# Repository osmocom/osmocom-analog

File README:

This software implements base station protocol of classic mobile phones. With
radio transmitter and receiver connected to one sound card and a headset
connected to another sound card, it is possible to make and receive calls to
and from mobile phone. With SDR (software defined radio) it can be use without
radio equipment connected to a sound card, and even multiple channels can be
generated simultaniously using SDR. Currently supported networks:

 * A-Netz
 * B-Netz (ATF-1)
 * C-Netz
 * NMT 450 / 900 (Nordic Mobile Telephone)
 * AMPS (Advanced Mobile Phone System)
 * TACS (Total Access Communication System)
 * JTACS (Japanese version of TACS)
 * Radiocom 2000 (French network)
 * IMTS / MTS ((Improved) Mobile Telephone Service)
 * MPT1327 (Trunked Radio) aka known as 'Buendelfunk'
 * Eurosignal (ERuRD paging service)
 * 5-Ton-Folge (ZVEI 5 tone paging code for pager and siren trigger)
 * JollyCom (Unofficial network, invented by the author)
 * C-Netz BSC (Connecting to a C-Netz Base Station)

Additionally the following communication services are implemented:

 * TV Transmitter with test Images
 * Radio transmitter / receiver
 * Analog Modem Emulation 'Datenklo' (AM7911)
 * German classic 'Zeitansage' (talking clock)
 * POCSAG transmitter / receiver
 * Golay/GSC transmitter / receiver
 * DCF77 time signal transmitter and receiver with weather info
 * C-Netz SIM emulator
 * C-Netz magnetic card emulator

USE AT YOUR OWN RISK!

Acknowledgements:

Carsten Wollesen for donating Telefunken 4015 B-Netz phone back in the 90's.

Klaus Adler for helping me to retrieve complete NMT specification and donating
a BSA44 (magnetic card C-Netz hackable phone) back in the 90's.

Andy Zauner for providing signaling specification of C-Netz back in the 90's.

Hans Wigger for providing valuable information about A-Netz and B-Netz and
helping me to get an A-Netz phone.

Stephan Hessberger for his work on oebl.de, that provides valuable information
about A-Netz, B-Netz, C-Netz, Eurosignal and much more.

Friedhelm Hillebrand for providing complete specification of the mobile phone
of C-Netz.

Mikko Ristila for providing newer NMT specs (with DMS/SMS specifications).

Dieter Spaar and Mark Atherton for providing AMPS information and recordings
to verify and debug AMPS support.
See http://www.idesignz.org/AMPS/AMPS_BS.html for first base station
implementation of AMPS.

Telecommunication Industry Association for providing TIA/EIA-533 documentation.
"Reproduced under written permission from Telecommunications Industry
Association."

Eric from Smart Card World and Karsten Niehusen from cardomatic.de for
providing memory cards to be programmed for older C-Netz phone.

Dieter Spaar providing TACS recordings to verify and debug TACS support.

Hans Wigger providing Radiocom 2000 recordings, to reverse-enigineer the
standard, which seems not to exist anymore...

Peter, Peter, Friedhelm and Stephan for providing documentation and hardware
for C-Netz Base Station and other C-Netz documents.

Carsten Wollesen for donating MPT1327 radios and programming tools.

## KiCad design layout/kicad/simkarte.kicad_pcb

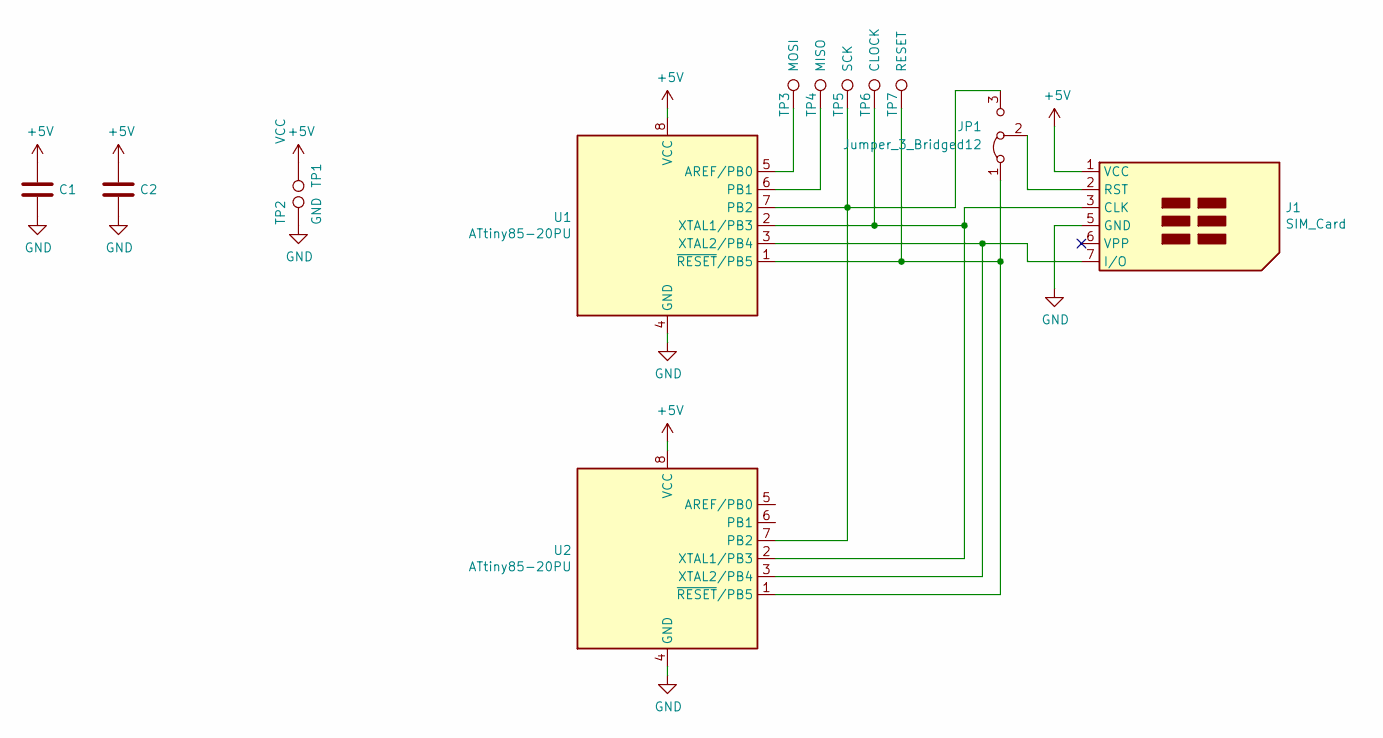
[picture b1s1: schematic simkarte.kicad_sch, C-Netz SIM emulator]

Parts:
C1, C2: C; C_0603_1608Metric
J1: SIM_Card; SIM-Pads
JP1: Jumper_3_Bridged12; SolderJumper-3_P1.3mm_Bridged12_RoundedPad1.0x1.5mm_NumberL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
TP1: VCC; tp_for_sim
TP2: GND; tp_for_sim
TP3: MOSI; tp_for_sim
TP4: MISO; tp_for_sim
TP5: SCK; tp_for_sim
TP6: CLOCK; tp_for_sim
TP7: RESET; tp_for_sim
U1: ATtiny85-20PU; SO-8_falschrum
U2: ATtiny85-20PU; DIP-8_W7.62mm_Socket

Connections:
+5V: C1.1, C2.1, J1.1 (VCC), TP1.1, U1.8 (VCC), U2.8 (VCC)
GND: C1.2, C2.2, J1.5 (GND), TP2.1, U1.4 (GND), U2.4 (GND)
unnamed: J1.2 (RST), JP1.2 (C)
unnamed: J1.3 (CLK), TP6.1, U1.2 (XTAL1/PB3), U2.2 (XTAL1/PB3)
unnamed: J1.7 (I/O), U1.3 (XTAL2/PB4), U2.3 (XTAL2/PB4)
unnamed: TP3.1, U1.5 (AREF/PB0)
unnamed: TP4.1, U1.6 (PB1)
unnamed: JP1.3 (B), TP5.1, U1.7 (PB2), U2.7 (PB2)
unnamed: JP1.1 (A), TP7.1, U1.1 (~RESET/PB5), U2.1 (~RESET/PB5)

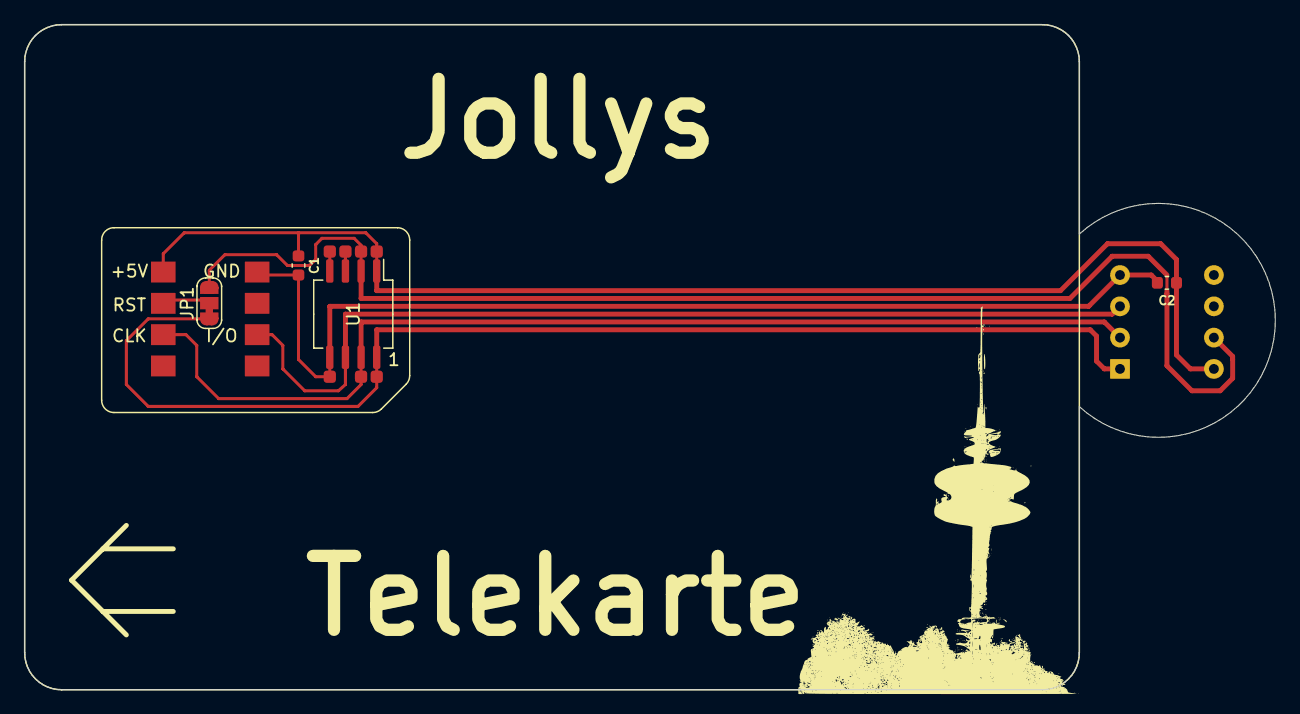
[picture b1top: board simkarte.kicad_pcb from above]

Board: 2 copper layers, 101.5 x 54.0 mm, 13 parts (1 on the bottom side), 9 nets.

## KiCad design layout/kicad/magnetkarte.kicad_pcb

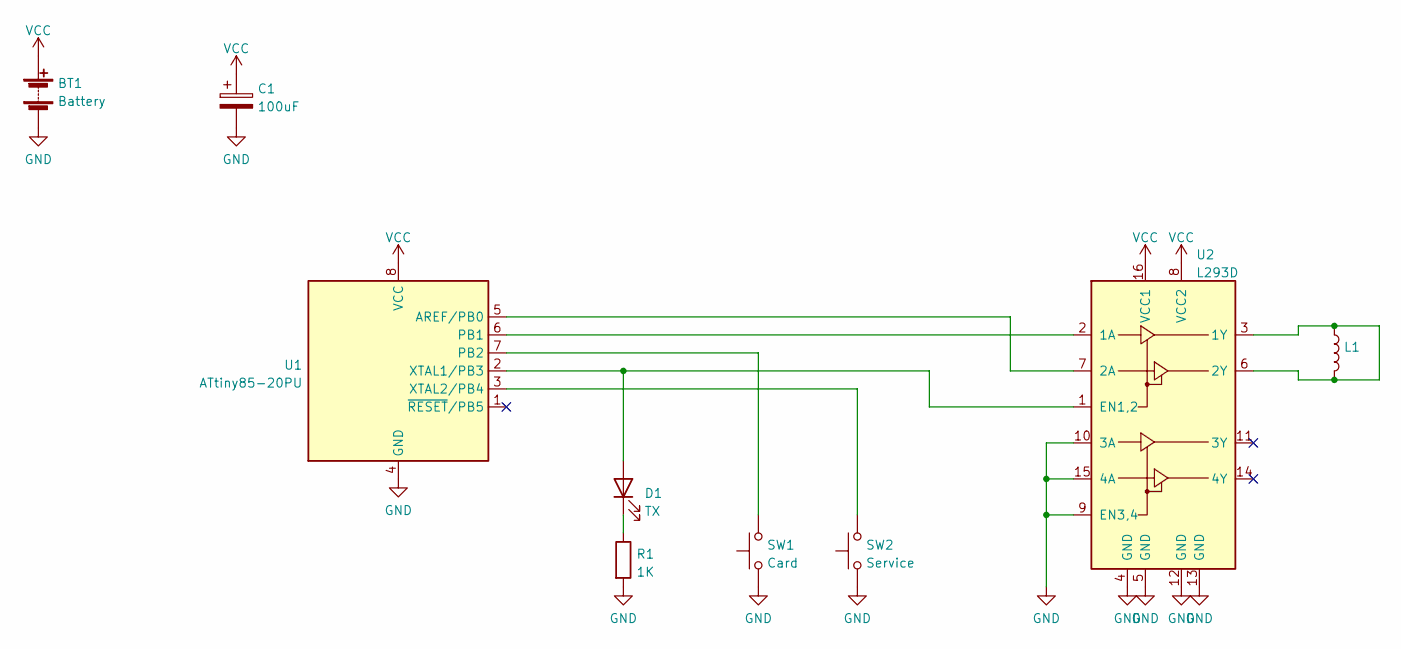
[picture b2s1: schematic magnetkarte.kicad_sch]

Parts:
BT1: Battery; PinHeader_2x01_P2.54mm_Vertical
C1: 100uF; CP_Radial_D6.3mm_P2.50mm
D1: TX; LED_D3.0mm_Clear
L1: L; PinHeader_2x01_P2.54mm_Vertical
R1: 1K; R_Axial_DIN0207_L6.3mm_D2.5mm_P10.16mm_Horizontal
SW1: Card; SW_PUSH_6mm_H4.3mm
SW2: Service; SW_PUSH_6mm_H4.3mm
U1: ATtiny85-20PU; DIP-8_W7.62mm
U2: L293D; DIP-16_W7.62mm

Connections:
GND: BT1.2 (-), C1.2, R1.2, SW1.1, SW2.1, U1.4 (GND), U2.4 (GND), U2.5 (GND), U2.9 (EN3,4), U2.10 (3A), U2.12 (GND), U2.13 (GND), U2.15 (4A)
unnamed: D1.1 (K), R1.1
unnamed: D1.2 (A), U1.2 (XTAL1/PB3), U2.1 (EN1,2)
unnamed: L1.1, L1.2, U2.3 (1Y), U2.6 (2Y)
unnamed: SW1.2, U1.7 (PB2)
unnamed: SW2.2, U1.3 (XTAL2/PB4)
unnamed: U1.5 (AREF/PB0), U2.7 (2A)
unnamed: U1.6 (PB1), U2.2 (1A)
VCC: BT1.1 (+), C1.1, U1.8 (VCC), U2.8 (VCC2), U2.16 (VCC1)

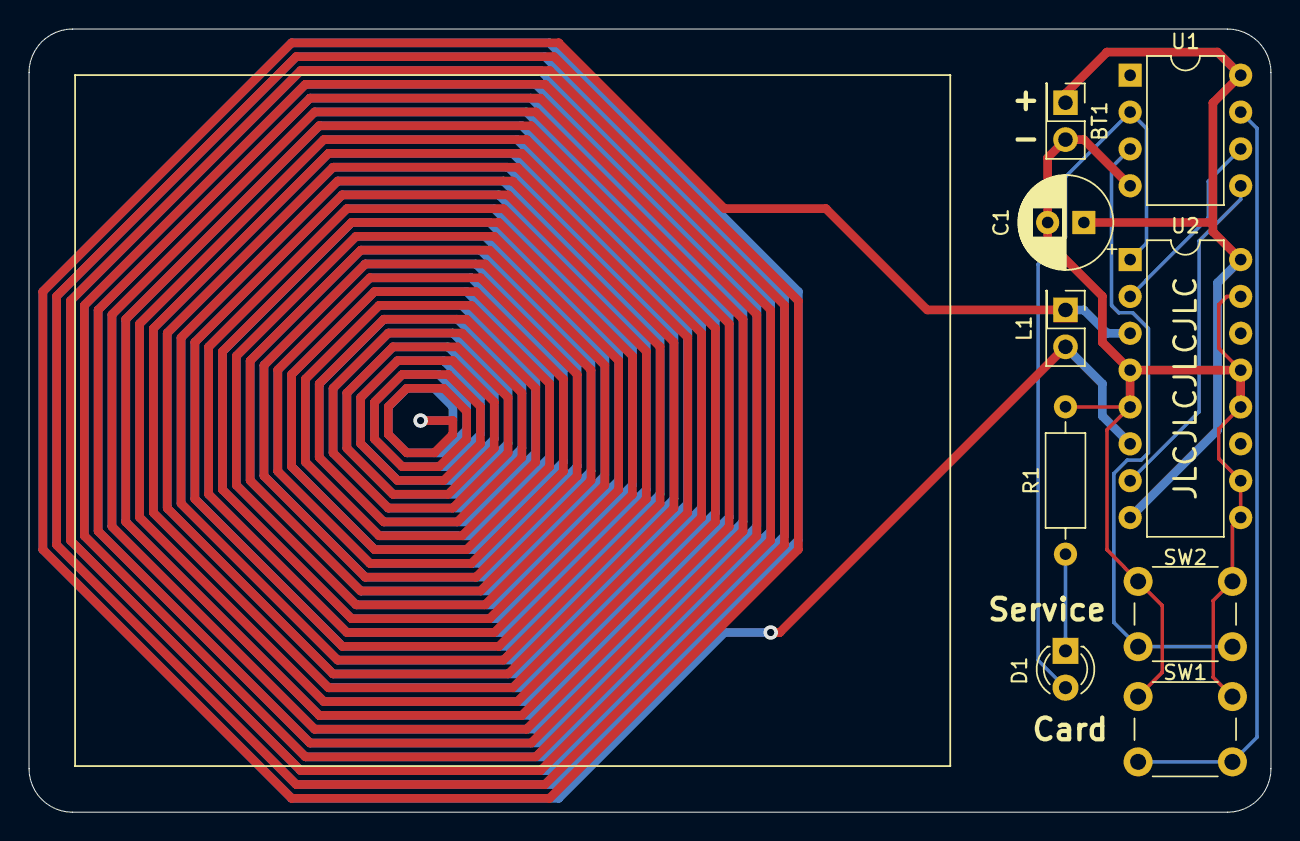
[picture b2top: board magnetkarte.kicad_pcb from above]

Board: 2 copper layers, 85.6 x 54.0 mm, 9 parts (0 on the bottom side), 9 nets.

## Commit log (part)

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2017-11-25 Restructure: Move fm_modulation from common code to 'libfm'
2017-11-25 Restructure: Move compandor from common code to 'libcompandor'
2017-11-25 Restructure: Move sound from common code to 'libsound'
2017-12-03 Restructure: Move mobile from common code to 'libmobile'
2017-12-03 Restructure: Fixing library linking order
2017-12-03 FM modulation: Never turn carrier completely off
    This prevents IIR filter to become very slow for some unknown reason.
2017-12-05 B-Netz: Minor fixes to timings and debug messages
2017-12-09 SDR: Add option to set local oscillator (LO) offset
    By default it is set to -1 MHz.
2018-02-15 NMT: Fixes on channel coding/handling
2018-02-15 Make sound card support (Alsa) optional
2018-02-15 work on docs
2018-02-15 B-Netz: Some cleanups
2018-02-16 remove obsolete function
2018-02-16 Improved audio (sdr) handling
2018-02-16 Add 'osmoradio', an analog radio (FM/AM)
    This radio can be a receiver or a transmitter or both simultaniously.
2018-05-21 Osmoradio fixes: Use real time scheduling and always transmit empty buffer
2018-05-21 Refactoring command line option handling
    * Use own function to define and parse command line options
    * Command line options can be defined by config file also
    * --limesdr allows to auto-set required SDR option for LimeSDR
2018-05-21 C-Netz: Fixed display of states (state display function)
2018-06-05 B-Netz: Refactoring tone and quality detection
2018-06-24 TV: Minor code cleanup
2018-08-25 SDR: Fix level range of IQ date; must not exceed range of -1 .. 1
    LimeSDR mini (and maybe others) do not want IQ data to become a value below
    -1 or above 1. This happens slightly when applying the IIR filter after
    upsampling. To prevent this, we scale down the IQ level a little bit.
    To test the problem:
    - set the scale level to 1.0, so it does not take effect
    - use LimeSDR mini
2018-08-26 C-Netz: Allow SDR using C-Netz without calibration options
    Crystals on SDRs are accurate enough for C-Netz (< 1ppm).
2018-10-30 NMT: Fix channel encoding for interleaved
2018-11-10 Radio: Minor fixes
2018-12-23 B-Netz: Add base stations of the Netherlands
2019-01-02 C-Netz: Add option to control voice deviation
2019-05-12 OsmoTV: Added more test patterns for TV repair
    - improved FUBK
    - red screen for DY adjustment
    - crosses and dots for convergence adjustment
    - EBU color bars
    - natural color image
2019-05-30 SDR: Move center frequenc (DC) away from channels
    If one channel is used, shift the center frequency down by half of the bandwidth.
    If more channels are used, select a center frequency between two channels close to the center, but equal distance.
    Show the spectum layout on startup.
    This patch reverts f1292a985bf8f19d9538e6337c229db1b463a547
2019-06-30 Output ASCII art image after all init functions (inside main_mobile.c)
2019-07-06 Allow dialing national and international prefix for AMPS/TACS
2019-08-26 Allow giving alphanumeric channels (Prepare for IMTS)
2019-08-26 Remove useless debug lines
2019-08-26 Fixed performance issue with IIR filter
    Passing samples with zero value (0.0) causes very slow processing of
    IIR filter on my test machine 'nuedel'. I don't know why.
    To solve this, I add a very small number to each input sample.
2019-10-26 C-Netz: Fixup for broken Authentication patch
    MT calls did not work.
2019-11-29 FSK demodulator: Also report bits that have duration < 0.5
2019-11-29 C-Netz: Added list of base station names and IDs
    Automatic polarity detection is now done by using the polarity of last
    transmitted message. We cannot use two base station IDs anymore, to
    detect the polarity. Now we deal only with the defined base station ID.
2019-11-29 Describe if audio device exists, but does not support both directions
2019-11-29 Modem emulator for "Datenklo" with AM7910/AM7911 emulation
2019-12-08 Rename dbm0 (level) to speech (level)
    In mobile communications we use speech level instead of milliwatts.
    The deviation (FM) is always based on speech level, not on 1 milliwatt.
2019-12-10 Add support for "Eurosignal", a classic paging service
2019-12-22 osmoradio: Play audio and record wave simultaniously
2020-01-02 C-Netz: --ms-power defines power level (not P-bits)
    Also the level 8 can be selected. Actually level 6 is selected, but
    reduced to 8 when making a call.
2020-01-12 Fixed compiler error for old GCC
2020-01-18 Implementation of German "Zeitansage", spoken by Elvira Bader
2020-03-27 Eurosignal: Allow dialing (paging) of Spare Digits
2020-05-23 Added local library for serial port access
2020-05-24 Added SIM card emulator/sniffer for C-Netz
2020-10-29 SIM: Fix output of numbers >32767 when using EBD program mode
    A shift of an unsigned char is interpreted as signed char, which causes
    all bits above the shift result to become 1, if bit 7 of the char is 1.
2020-10-29 C-Netz: At correct timeslot switch channel mode
    Without this, the first BQ(K) message came to early, so that BSA 51
    released when receiving ZFZ(K) one frame too early.
2020-10-29 C-Netz: Display "Bahn MS", "Bahn BS" and "Datenbetrieb" with messages
2020-10-29 Allow disabling MNCC Console when using a digit length of 0
2020-10-29 Add tx-gain option
2020-10-29 DTMF: Correctly handle frequency marging (percent not hertz!)
2020-10-29 AMPS: Suggest to use channel 333 (SID 1 = Chicago) by default
    Channel 334 seems to make Problems with my Dynatac.
2020-10-29 Zeitansage: Disable SDR
2020-12-21 C-Netz: Implementation of a Funkvermittlungsstelle (FuVSt)
    Useful to connect with a Funkfeststation (FuFSt).
2020-12-21 C-Netz: Fix scheduling of frames when there is nothing to send
2020-12-29 Replaced MNCC by OSMO-CC
2021-01-03 OsmoCC: Limit number of default socket ports to 20
2021-03-07 Added special strdup to liboptions, to prevent memory leaks for option strings
    If you are doing memory leak debugging you don't want to see any leaks when
    stopping the program.
2021-03-07 osmo-cc: Improve network type information element
2021-03-20 Fix some minor compiling issues
2021-03-20 Osmo-CC: The 'local' socket peer is also used as default rtp-peer
2021-03-28 Make Alsa sound interface indipendent from libmobile
2021-04-03 libosmocc: Add support for individual session config (per endpoint)
2021-06-06 Working on Docs
2021-06-23 SoapySDR: Fixed API change from version 0.7.1
2021-09-17 C-Netz: Updated base station list
2021-09-17 Osmo-CC: Conversion function between values and their names
    Allows to convert integer values into their names and vice versa.
2021-09-24 Added locking to debug output, to prevent race condition between threads
2021-11-07 Refactoring ASCCI-Art image printing
2021-11-07 AMPS: Fixed minor compiler warning
2021-11-07 SoapySDR: Fixed API change from version 0.8.0
    The last API check was wrong. 0.7.2 is still old api, but 0.8.0 is new.
2021-11-07 Refactoring validity check and prefix processing of dialed number
    Command line help shows how many digits and what prefixes can be dialed.
    Giving a station ID via command line will be checked for being valid.
    The number to call the mobile statione will be checked for being valid.
    Prefixes that are defined for a nework will be removed from station ID
    automatically.
    Multiple station ID lengths are supported:
2021-11-07 Correctly show channel frequencies in spectrum view when swapping SDR links
2021-12-08 Improvement of Goertzel filter. Using Hamming window now. Add test routine.
2021-12-12 SoapySDR: Minor debug output improvement
2021-12-12 When a transmitter is off, send absolutely nothing
    This is done by shifting away the transmitter from center (DC) freqency.
    Useless code was removed, since there is nothing to be transmitted.
2021-12-30 Osmo-CC: Correctly bind to local IP address, rather than any IP
2022-05-29 ALSA: Add environment variable to delay input
    This helps to avoid corrupted date in rx buffer.
    Sorry: No more info, because I really don't know why this happens.
2022-06-18 debug: Show debug category together with debug level
2022-06-18 Implementation of DCF77 transmitter and receiver
2022-06-19 C-Netz: Add capability of special tunnel base station (bahn-bs)
    Totally useless, if you don't have a train phone - don't you?
2022-06-19 C-Netz: Fix station list and selection
2022-06-19 R2000: Show debugging for IDLE frames
    Suppress repeated IDLE frame
2022-06-25 Osmo-CC: Option to override interface name given by application
2022-07-23 NMT: Fixes to 'additional info' and added clock (time) support
    - untested -
2022-07-23 Osmo-CC: Minor 'cause conversion' fix
2022-07-23 C-Netz: Improved RX speech quality and decoder debugging
2022-09-10 AMPS: Caller ID Support
    Support for sending caller ID for newer phones.
    Currently does not work with older phones, they will abort.
2022-09-15 Fixed README
2022-09-17 Improved libsamplerate to allow size calculations
2022-10-23 libsample: Add another function for converting between int16_t and sample_t
    Now we have speech level and 1mW (0 dBm) conversion functions
2022-10-23 Osmo-CC: Add marker bit support
2022-10-30 Golay/GSC paging support
2022-11-07 TACS: Corrected TACS power levels in help description
2022-11-24 osmo-cc: Set session to NULL, if no codec matches
    Applications will crash, due to use-after-free bug, if this is not done.
2022-12-16 Fixed a bug on datenklo's ioctrls
2022-12-16 FSK modulator improvements
    1. Phase is now changed proportional to the time of the bit change, if
    it happens somewhere between samples. The amount of phase change per
    bit is now the same for all bits, no matter how many samples
    currently lay inside this bit.
    2. IIR filter is removed, because it causes distortions. A cosine shape
    is now used to transit between phase change of F0 to F1 and vice
2023-01-21 Make libdebug osmocore complatible in some places
2023-01-22 Changed logging of libosmocc to osmocom style
2023-03-26 libosmo-cc: Allow remote port change with RTP
    In case of port translation, the different remote RTP port is adopted
    for further transfer.
    This happens, if remote peer uses NAT that changes source port also.
2023-06-10 Osmo-CC: Add R1 interface type
2023-08-27 C-Netz: Updated sim card layout to support memory card emulation.
    A jumper must be switched in order to emulate the reset input.
    Also added new service codes to the silk mask.
2023-09-10 C-Netz-SIM: Store version number in phone book entry 01 as default.
2023-10-08 [NMT] fix UA UMC country code
2023-11-12 libosmocc: Flag codec as not accepted instead of removing it
    This is required if multiple SDP responses are returned. We don't want
    to remove a codec with with the first SDP response, which might get
    accepted by the second SDP response. Instead we flag the codec as
    negotiated or not negotiated.
    When early media is received, different codecs may be accepted as when
    we receive the actual answer.
2023-11-27 G711: Fix bitorder of u-law codec
    Tested with Grandstream
2024-01-04 Fix usage of strncat
2024-02-18 Add help about settings at location area overheade message
2024-02-18 Add "--no-config" option, to ignore existing default config file
2024-02-18 FuVst: Add security code and card reader type to database
2024-02-18 Add metering information from osmo-cc to B-Netz and C-Netz
    Untested!
2024-03-25 Fix buffer overflow when displaying measurements
2024-03-30 A different recording device may be specified for sound card access
2024-03-30 Improve image of IMTS
2024-03-30 Fix command to list channel on various networks
2024-04-05 C-Netz SIM: Fix entering card numbers with leading zeroes
    Numbers for the SIM card can be entered with zeroes in the front. This
    will not change numbers to octal. The Bosch OF 7 phone will not accept
    numbers in the phone book with less than 4 digits, so it is essential to
    allow entering numbers with zeroes in front.
    Also state that in the documents.
2024-04-10 Fix filter of demodulator of received radio signal
    The filter was way too low. (only half of the total bandwidth)
    The missing (filtered) high frequency component caused noisy signal.
    Let's see how this fix changes the quality of received FM sound.
2024-04-13 SIM: Display SIM version in programming mode on memory location 06
    Untested!
2024-04-21 POCSAG: Allow all 128 ASCII characters to be transmitted
    To allow all 128 ASCII characters, a null-terminated string cannot be
    used. Instead a length is used to define string length, to allow
    null-character in that the message string.
    The print function in frame.c is improved and used to present the
    string.
2024-05-07 DCF77: Disable the display on exit
2024-05-07 Support both versions of ImageMagick: 6 and 7
2024-08-12 C-Netz: Update anouncement to better quality version
2024-08-18 R2000: Add "out of order" audio output
2024-09-08 AMPS: Add interleaved channels starting with X
    Source:
    https://telephoneworld.org/cellular-phone-history/pre-cellular-mts-imts/
2025-01-05 Eurosignal: Add ROM description for E300 pagers
2025-01-15 Fix compiler warnings and error on all configuration combination
2025-11-20 Add safe strlcpy/strlcat, snprintf is already safe
